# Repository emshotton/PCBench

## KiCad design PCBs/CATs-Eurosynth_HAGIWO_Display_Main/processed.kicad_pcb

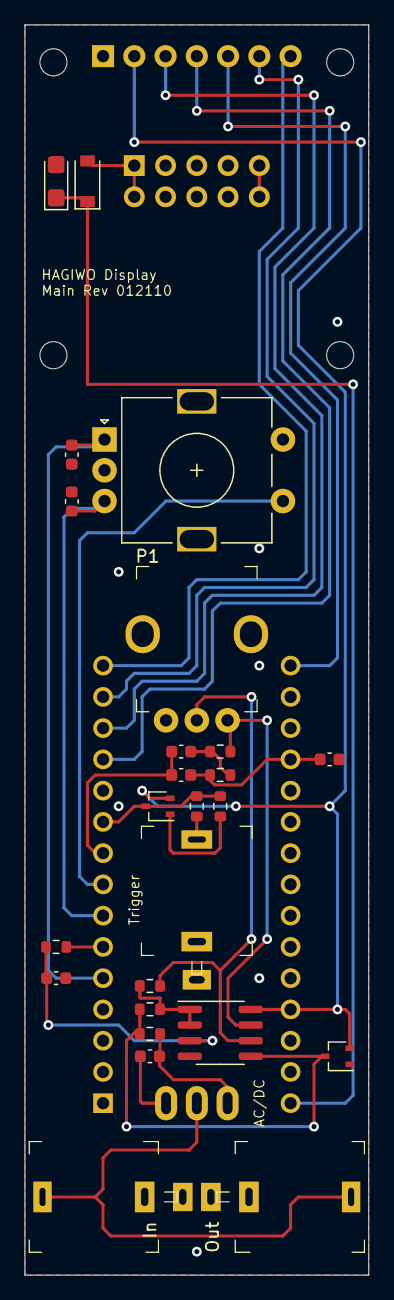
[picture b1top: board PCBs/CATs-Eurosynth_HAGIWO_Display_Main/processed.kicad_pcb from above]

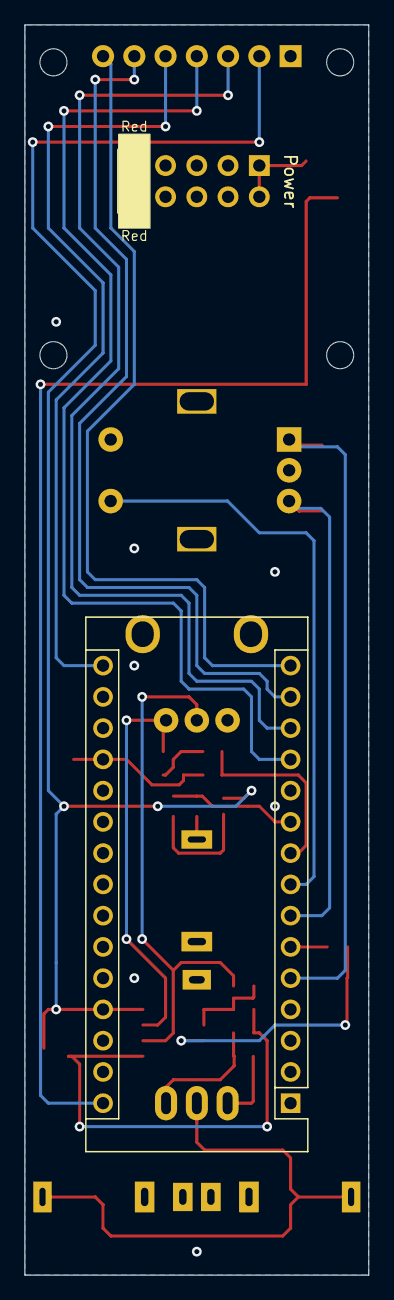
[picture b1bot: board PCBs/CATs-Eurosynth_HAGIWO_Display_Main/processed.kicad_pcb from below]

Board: 2 copper layers, 27.9 x 101.6 mm, 33 parts (2 on the bottom side), 26 nets.

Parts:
A1: Arduino_Nano_v3.x; Arduino_Nano
C1: 10µF/16V; CP_EIA-3216-18_Kemet-A
C2: 1µF; C_0603_1608Metric
C3: 4.7µF; C_0603_1608Metric
C4, C5: 22n; C_0603_1608Metric
C6: 470p; C_0603_1608Metric
C7, C8: 10n; C_0603_1608Metric
D1: B5817W; D_SOD-123
D2, D3: BAV99W; SOT-323_SC-70
DISP1: MSP096x
H1, H2, H3, H4: MountingHole; MountingHole_2.2mm_M2
J1: Power; Power_2x5_Vertical
J2: Trigger; Jack_3.5mm_QingPu_WQP-PJ301M-12
J3: In; Jack_3.5mm_QingPu_WQP-PJ301M-12
J4: Out; Jack_3.5mm_QingPu_WQP-PJ301M-12
P1: B100k; Potentiometer_AlpsAlpine_RK09K1130
R1, R5: 47k; R_0603_1608Metric
R2, R7, R8: 1k; R_0603_1608Metric
R3: 100k; R_0603_1608Metric
R4, R6: 10k; R_0603_1608Metric
SW1: AC/DC; SMTS-102-2xxx
SW2: Encoder; RotaryEncoder_Alps_EC11E-Switch_Vertical_H20mm
U1: MCP6002-xSN; SOIC-8_3.9x4.9mm_P1.27mm

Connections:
+5V: A1.27, D2.2, D3.2, DISP1.VCC, U1.8
+12V: A1.30, C1.1, D1.1
+12VA: D1.2, J1.+12V
CS: A1.15, DISP1.CS
DC: A1.14, DISP1.DC
DI: A1.12, DISP1.DI
DO: A1.13, DISP1.DO
ENC_A: A1.5, C7.1, SW2.A
ENC_B: A1.7, C8.1, SW2.B
ENC_SW: A1.8, SW2.S1
Fast_PWM: A1.6, R1.2
GND: A1.4, A1.29, C1.2, C2.2, C6.2, C7.2, C8.2, D2.1, D3.1, DISP1.GND, J1.GND, J2.S, J2.TN, J3.S, J3.TN, J4.S, R3.1, SW2.C, SW2.S2, U1.4
In: A1.19, C5.1, C6.1, R8.1
LPF_Enable: A1.9, C4.2, C5.2
unnamed: C2.1, R1.1, U1.3
unnamed: C3.1, R5.2, SW1.1
unnamed: C3.2, SW1.3
unnamed: C4.1, R7.1, R8.2
unnamed: D3.3, R4.2, R5.1, U1.5
unnamed: J2.T, R2.2
unnamed: J3.T, J4.T, SW1.2
unnamed: P1.CW, R7.2, U1.7
unnamed: P1.W, R6.2, U1.6
Offset: R4.1, R6.1, U1.1, U1.2
RST: A1.16, DISP1.RESET
TriggerIn: A1.10, D2.3, R2.1, R3.2

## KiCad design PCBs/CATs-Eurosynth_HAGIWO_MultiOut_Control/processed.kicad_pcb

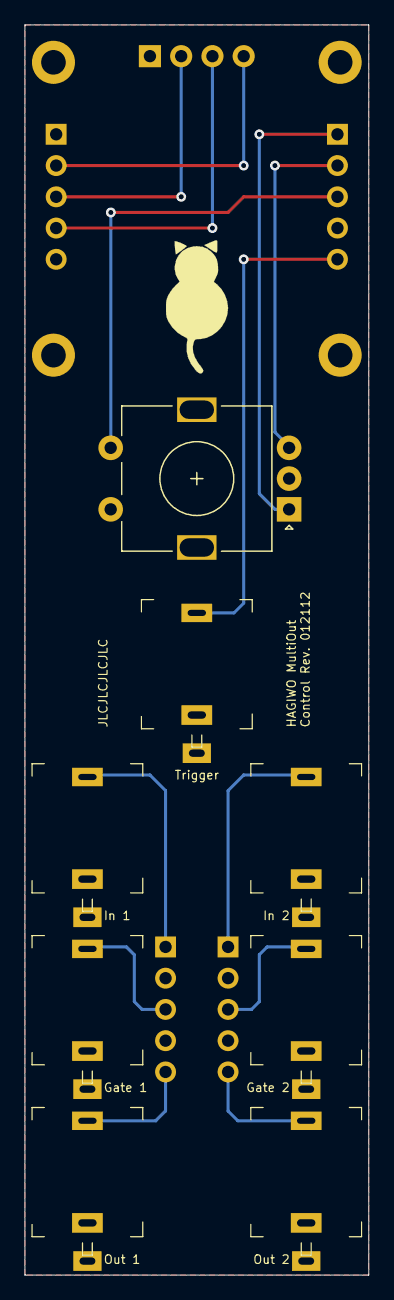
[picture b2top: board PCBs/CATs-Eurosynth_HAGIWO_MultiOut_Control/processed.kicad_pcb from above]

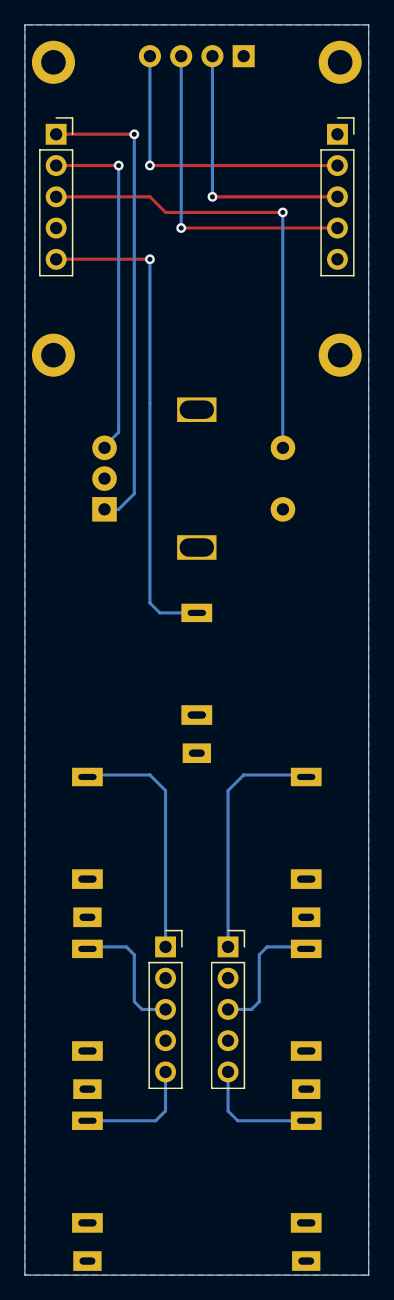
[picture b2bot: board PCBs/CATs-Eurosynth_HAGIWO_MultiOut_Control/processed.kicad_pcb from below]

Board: 2 copper layers, 27.9 x 101.6 mm, 13 parts (4 on the bottom side), 14 nets.

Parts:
D1: SSD1306_4Pin; 0.96inch_OLED_MC096GX
J1: Trigger; Jack_3.5mm_QingPu_WQP-PJ301M-12
J2: In 1; Jack_3.5mm_QingPu_WQP-PJ301M-12
J3: Gate 1; Jack_3.5mm_QingPu_WQP-PJ301M-12
J4: Out 1; Jack_3.5mm_QingPu_WQP-PJ301M-12
J5: In 2; Jack_3.5mm_QingPu_WQP-PJ301M-12
J6: Gate 2; Jack_3.5mm_QingPu_WQP-PJ301M-12
J7: Out 2; Jack_3.5mm_QingPu_WQP-PJ301M-12
J8: EncTrig; PinSocket_1x05_P2.54mm_Vertical
J9: Ch. 1; PinSocket_1x05_P2.54mm_Vertical
J10: Ch. 2; PinSocket_1x05_P2.54mm_Vertical
J11: I2C; PinSocket_1x05_P2.54mm_Vertical
SW1: Enc; RotaryEncoder_Alps_EC11E-Switch_Vertical_H20mm

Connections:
+3V3: D1.VCC, J11.3
Enc_A: J8.1, SW1.A
Enc_B: J8.2, SW1.B
Enc_SW: J8.3, SW1.S1
GND: D1.GND, J1.S, J1.TN, J2.S, J2.TN, J3.S, J4.S, J5.S, J5.TN, J6.S, J7.S, J8.4, J9.2, J9.4, J10.2, J10.4, J11.1, J11.5, SW1.C, SW1.S2
Gate1: J3.T, J9.3
Gate2: J6.T, J10.3
In1: J2.T, J9.1
In2: J5.T, J10.1
Out1: J4.T, J9.5
Out2: J7.T, J10.5
SCL: D1.SCL, J11.4
SDA: D1.SDA, J11.2
Trigger: J1.T, J8.5

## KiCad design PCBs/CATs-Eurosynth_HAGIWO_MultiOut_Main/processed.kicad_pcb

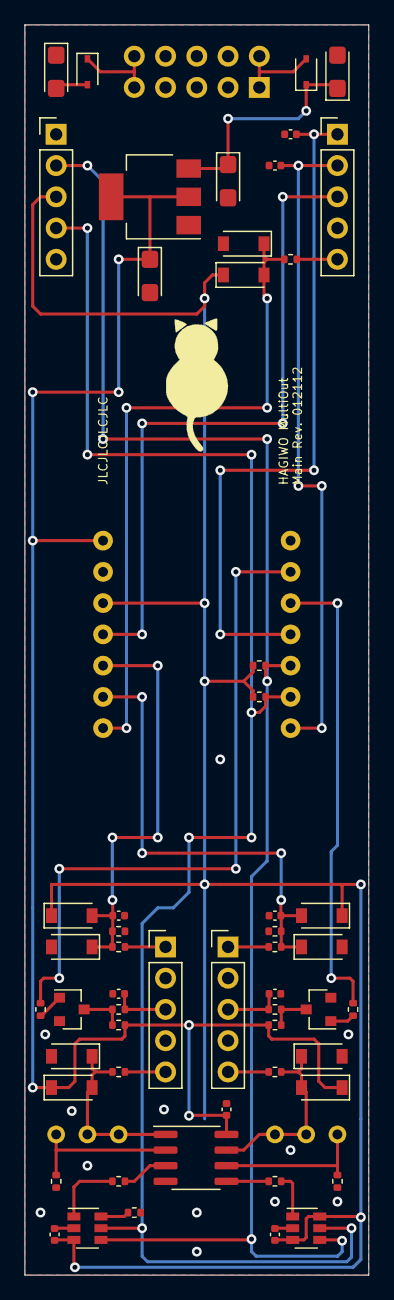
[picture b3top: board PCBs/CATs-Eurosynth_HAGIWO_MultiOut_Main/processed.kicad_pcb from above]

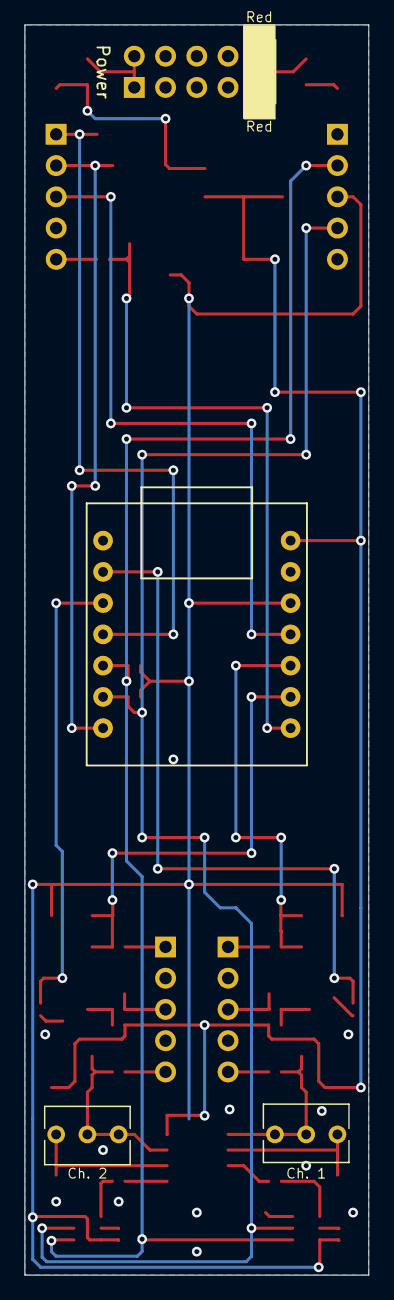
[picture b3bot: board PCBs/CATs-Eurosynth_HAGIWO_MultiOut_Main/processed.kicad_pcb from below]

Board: 2 copper layers, 27.9 x 101.6 mm, 59 parts (4 on the bottom side), 37 nets.

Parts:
C1, C2, C3, C4: 10µ; CP_EIA-3216-18_Kemet-A
C5, C6, C7, C8: 10n; C_0402_1005Metric
C9, C10: 1µ; C_0402_1005Metric
C11, C12, C13: 100n; C_0402_1005Metric
D1, D2: 1N5819WS; D_SOD-323
D4, D5, D6, D7, D8, D9, D10, D11, D12, D13: BAT43W; D_SOD-123
J1: Power; Power_2x5_Vertical
J9: EncTrig; PinHeader_1x05_P2.54mm_Vertical
J10: Ch. 1; PinHeader_1x05_P2.54mm_Vertical
J11: I2C; PinHeader_1x05_P2.54mm_Vertical
J12: Ch. 2; PinHeader_1x05_P2.54mm_Vertical
Q1, Q2: MMBT3904; SOT-23
R1, R2: 3k3; R_0402_1005Metric
R3, R16, R20: 10k; R_0402_1005Metric
R4, R17: 6k8; R_0402_1005Metric
R5, R6: 220k; R_0402_1005Metric
R7, R8: 330k; R_0402_1005Metric
R9: 33k; R_0402_1005Metric
R10, R11: 1k; R_0402_1005Metric
R12, R13, R14, R15: 330R; R_0402_1005Metric
R18, R19: 470R; R_0402_1005Metric
RV1, RV2: 5k; Potentiometer_Bourns_3266Y_Vertical
U1: AMS1117-5.0; SOT-223-3_TabPin2
U2: SeeeduinoXIAOPin; Seeeduino XIAO Pin
U3, U5: MCP4725xxx-xCH; SOT-23-6
U4: MCP6002-xSN; SOIC-8_3.9x4.9mm_P1.27mm

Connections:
+3V3: C11.1, C12.1, D4.1, D6.1, D8.1, J11.3, R1.1, R2.1, U2.12, U3.3, U5.3, U5.6
+5V: C4.1, C13.1, D10.1, D12.1, R12.1, R13.1, U1.2, U2.14, U4.8
+12V: C1.1, C3.1, D1.1, U1.3
-12V: C2.2, D2.2
A7: D8.2, D9.1, R9.1, U2.8
A8: C6.1, D6.2, D7.1, R6.1, R8.2, U2.9
A9: C5.1, D4.2, D5.1, R5.1, R7.2, U2.10
D1: R10.2, U2.2
D2: R11.2, U2.3
D3: C7.1, J9.1, U2.4
D6: C8.1, J9.2, U2.7
D10: J9.3, U2.11
GND: C1.2, C2.1, C3.2, C4.2, C5.2, C6.2, C7.2, C8.2, C9.2, C10.2, C11.2, C12.2, C13.2, D5.2, D7.2, D9.2, D11.2, D13.2, J1.GND, J9.4, J10.2, J10.4, J11.1, J11.5, J12.2, J12.4, Q1.2, Q2.2, R4.1, R7.1, R8.1, R17.1, R20.1, U1.1, U2.13, U3.2, U4.4, U5.2
Gate1: C9.1, J10.3, R14.1
Gate2: C10.1, J12.3, R15.1
In1: J10.1, R5.2
In2: J12.1, R6.2
unnamed: D1.2, J1.+12V
unnamed: D2.1, J1.-12V
unnamed: D10.2, D11.1, R18.2, RV1.1, RV1.2, U4.1
unnamed: D12.2, D13.1, R19.2, RV2.1, RV2.2, U4.7
unnamed: Q1.1, R10.1
unnamed: Q1.3, R12.2, R14.2
unnamed: Q2.1, R11.1
unnamed: Q2.3, R13.2, R15.2
unnamed: R3.1, U4.3
unnamed: R3.2, U3.1
unnamed: R4.2, RV1.3, U4.2
unnamed: R16.1, U4.5
unnamed: R16.2, U5.1
unnamed: R17.2, RV2.3, U4.6
unnamed: R20.2, U3.6
Out1: J10.5, R18.1
Out2: J12.5, R19.1
SCL: J11.4, R2.2, U2.6, U3.5, U5.5
SDA: J11.2, R1.2, U2.5, U3.4, U5.4
Trigger: J9.5, R9.2

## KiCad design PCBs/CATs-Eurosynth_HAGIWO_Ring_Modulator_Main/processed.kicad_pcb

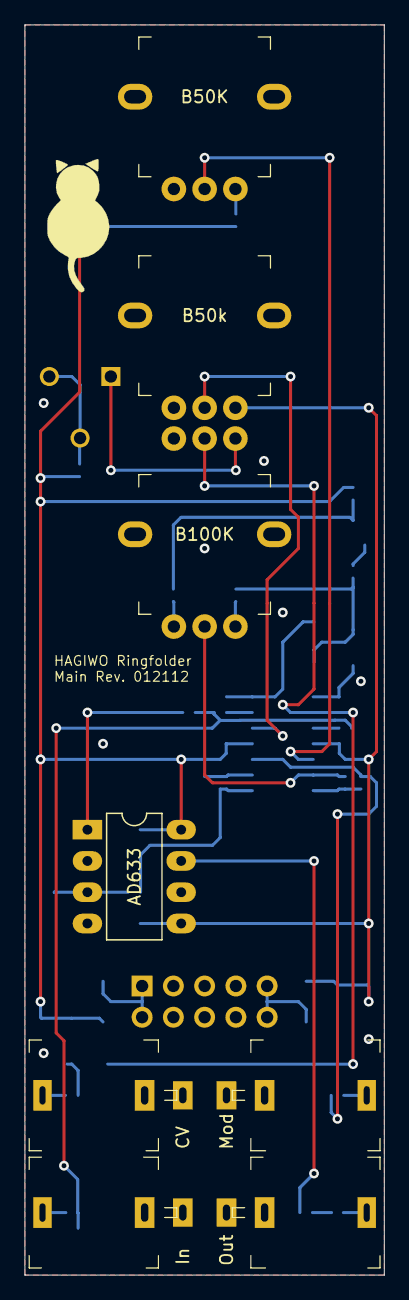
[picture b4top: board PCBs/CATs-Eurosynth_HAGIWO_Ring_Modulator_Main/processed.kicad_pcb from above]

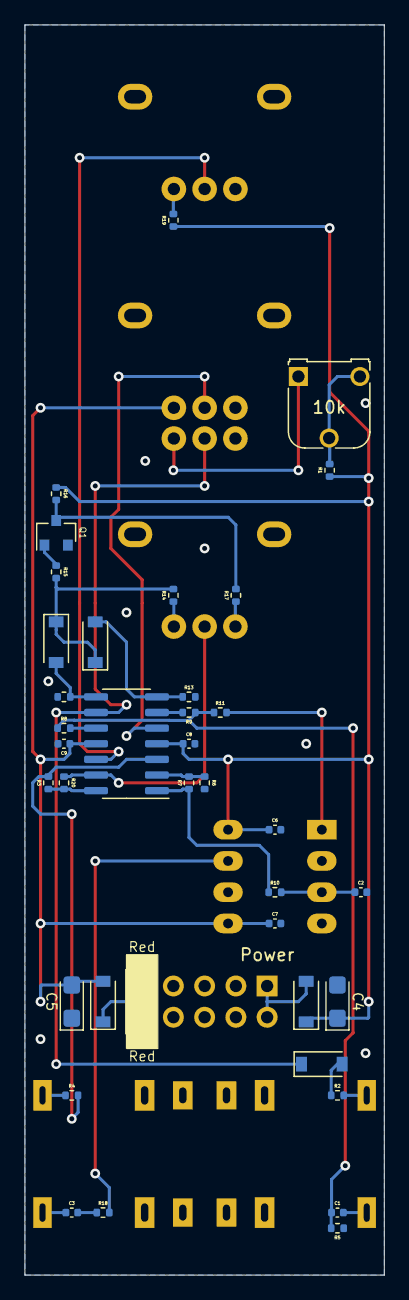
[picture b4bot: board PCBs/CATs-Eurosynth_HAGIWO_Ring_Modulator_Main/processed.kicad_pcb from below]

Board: 2 copper layers, 29.2 x 101.6 mm, 46 parts (38 on the bottom side), 35 nets.

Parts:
C1, C3: 1µ; C_0402_1005Metric
C2: 3n3; C_0402_1005Metric
C4, C5: 10µ/25V; CP_EIA-3216-18_Kemet-A
C6, C7, C8, C9: 100n; C_0402_1005Metric
D1, D2, D3: 1N4148; D_SOD-123
D4, D5: 1N5817; D_SOD-123
J1: CV; Jack_3.5mm_QingPu_WQP-PJ301M-12
J2: In; Jack_3.5mm_QingPu_WQP-PJ301M-12
J3: Mod; Jack_3.5mm_QingPu_WQP-PJ301M-12
J4: Out; Jack_3.5mm_QingPu_WQP-PJ301M-12
J5: Power; Power_2x5_Vertical
P1: B50k; Potentiometer_AlpsAlpine_RK09L1240
P2: B100K; Potentiometer_AlpsAlpine_RK09L1140
P3: B50K; Potentiometer_AlpsAlpine_RK09L1140
Q1: MMBT3904; SOT-23
R1, R2, R7, R10, R15: 10k; R_0402_1005Metric
R3, R4, R6, R8, R9, R11: 33k; R_0402_1005Metric
R5, R12, R13, R16, R20: 100k; R_0402_1005Metric
R14, R17, R19: 47k; R_0402_1005Metric
R18: 4k7; R_0402_1005Metric
T1: 10k; Potentiometer_Runtron_RM-065_Vertical
U1: AD633; DIP-8_W7.62mm_LongPads
U2: TL074; SOIC-14_3.9x8.7mm_P1.27mm

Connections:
+12V: C4.1, C6.2, C8.2, D4.1, R1.2, R16.2, R19.2, U1.8, U2.4
-12V: C5.2, C7.1, C9.1, D5.2, P1.CW1, U1.5, U2.11
Fold_In: R3.2, R20.1, U2.14
GND: C2.1, C4.2, C5.1, C6.1, C7.2, C8.1, C9.2, J1.S, J1.TN, J2.S, J2.TN, J3.S, J3.TN, J4.S, J5.GND, P1.CCW1, P1.CCW2, P3.CCW, Q1.2, R5.1, R6.1, R12.1, R13.1, U1.2, U1.4, U1.6
unnamed: C1.1, R5.2, R8.2, R9.2, R11.2
unnamed: C1.2, J2.T
unnamed: C2.2, R10.1, U1.3
unnamed: C3.1, J4.T
unnamed: C3.2, R18.1
unnamed: D1.1, P1.W2, U2.9
unnamed: D1.2, R2.1
unnamed: D2.1, D3.1, R14.2, R15.2
unnamed: D2.2, R12.2, U2.8
unnamed: D3.2, R13.2, U2.7
unnamed: D4.2, J5.+12V
unnamed: D5.1, J5.-12V
unnamed: J1.T, R2.2
unnamed: J3.T, R4.2
unnamed: P1.CW2, T1.1
unnamed: P1.W1, U2.5
unnamed: P2.CCW, R17.1
unnamed: P2.CW, R14.1
unnamed: P2.W, R20.2, U2.13
unnamed: P3.CW, R19.1
unnamed: P3.W, U2.12
unnamed: Q1.1, R15.1
unnamed: Q1.3, R16.1, R17.2
unnamed: R1.1, T1.2, T1.3
unnamed: R3.1, R4.1, U2.3
unnamed: R6.2, R7.2, U2.2
unnamed: R8.1, U2.10
unnamed: R9.1, U2.6
unnamed: R7.1, R10.2, U2.1
unnamed: R11.1, U1.1
unnamed: R18.2, U1.7

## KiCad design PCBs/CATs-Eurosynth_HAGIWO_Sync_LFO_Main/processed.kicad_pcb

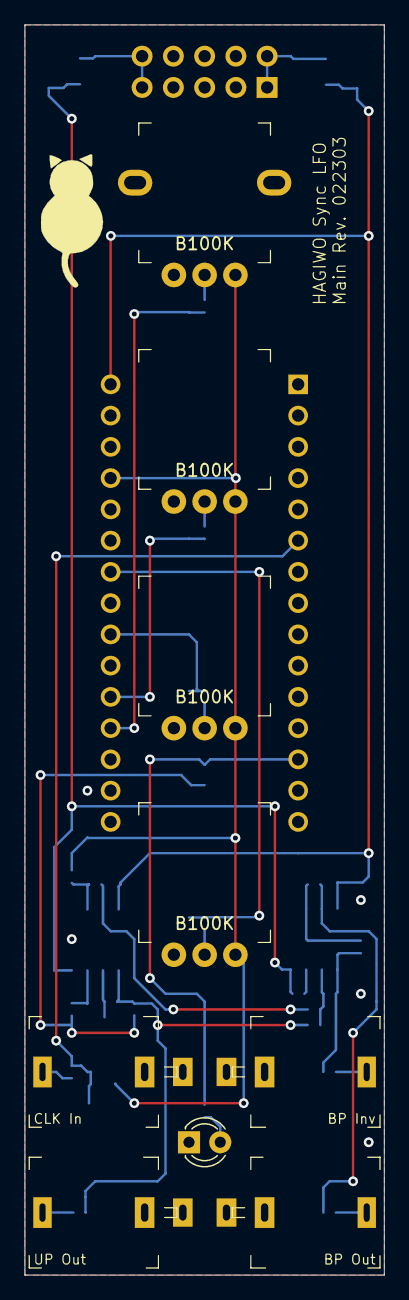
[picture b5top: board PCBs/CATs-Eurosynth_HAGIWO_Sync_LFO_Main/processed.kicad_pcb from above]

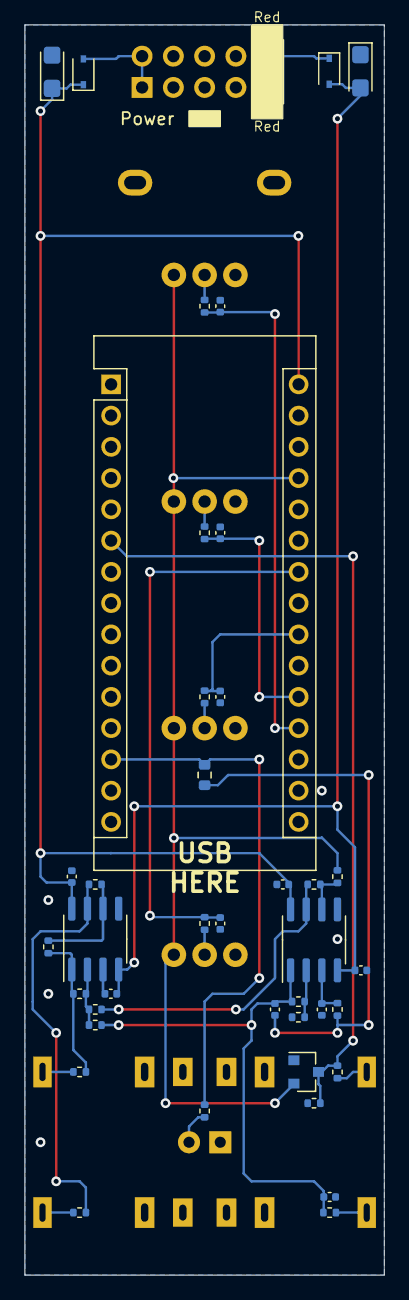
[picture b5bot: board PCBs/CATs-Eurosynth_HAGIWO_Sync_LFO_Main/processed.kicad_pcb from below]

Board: 2 copper layers, 29.2 x 101.6 mm, 50 parts (41 on the bottom side), 31 nets.

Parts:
A1: Arduino_Nano_v3.x; Arduino_Nano
C1, C2, C3, C4: 220p; C_0402_1005Metric
C5: 6.8n; C_0402_1005Metric
C6: 10n; C_0402_1005Metric
C7, C9, C10, C12, C13: 100n; C_0402_1005Metric
C8, C11: 10u; CP_EIA-3216-18_Kemet-A
D1: BAV99,215; SOT-23
D2: LED; LED_D3.0mm
D3, D4: 1N5819; D_SOD-323
J1: UP Out; Jack_3.5mm_QingPu_WQP-PJ301M-12
J2: CLK In; Jack_3.5mm_QingPu_WQP-PJ301M-12
J3: BP Inv; Jack_3.5mm_QingPu_WQP-PJ301M-12
J4: BP Out; Jack_3.5mm_QingPu_WQP-PJ301M-12
J5: Power; Power_2x5_Vertical
P1, P3, P4: B100K; Potentiometer_AlpsAlpine_RK09L1140_wo_Fix
P2: B100K; Potentiometer_AlpsAlpine_RK09L1140
R1, R2, R3, R4: 470R; R_0402_1005Metric
R5: 13k; R_0603_1608Metric
R6: 27k; R_0402_1005Metric
R7, R10, R16, R21: 1k; R_0402_1005Metric
R8: 300R; R_0402_1005Metric
R9, R11, R13, R14, R15, R17, R18, R19, R20: 10k; R_0402_1005Metric
R12: 100k; R_0402_1005Metric
U1, U2: TL072; SOIC-8_3.9x4.9mm_P1.27mm

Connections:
+5V: A1.27, D1.2, P1.CW, P2.CW, P3.CW, P4.CW, R18.2
+12V: A1.30, C8.1, C9.2, C10.2, D3.1, U1.8, U2.8
-5VA: R15.2, R17.1, U1.7
-12V: C11.2, C12.1, C13.1, D4.2, U1.4, U2.4
A0: A1.19, C2.1, R2.1
A1: A1.20, C3.1, R3.1
A3: A1.22, C1.1, R1.1
A5: A1.24, C4.1, R4.1
D3: A1.6, D1.3, R10.1, R12.2
D10: A1.13, R5.2, R8.2
GND: A1.4, A1.29, C1.2, C2.2, C3.2, C4.2, C6.1, C7.1, C8.2, C9.1, C10.1, C11.1, C12.2, C13.2, D1.1, D2.1, J1.S, J2.S, J2.TN, J3.S, J4.S, J5.GND, P1.CCW, P2.CCW, P3.CCW, P4.CCW, R11.1, R12.1, U1.5, U2.3, U2.5
unnamed: C5.2, R5.1, R6.2
unnamed: C6.2, R6.1, U1.3
unnamed: D2.2, R8.1
unnamed: D3.2, J5.+12V
unnamed: D4.1, J5.-12V
unnamed: J1.T, R7.1
unnamed: J2.T, R10.2
unnamed: J3.T, R16.1
unnamed: J4.T, R21.1
unnamed: P1.W, R1.2
unnamed: P2.W, R2.2
unnamed: P3.W, R3.2
unnamed: P4.W, R4.2
unnamed: R9.2, R11.2, U1.2
unnamed: R13.1, R14.2, R15.1, U2.2
unnamed: R14.1, R16.2, R20.2, U2.1
unnamed: R17.2, R18.1, U1.6
unnamed: R19.1, R21.2, U2.7
unnamed: R19.2, R20.1, U2.6
Out: C5.1, C7.2, R7.2, R9.1, R13.2, U1.1

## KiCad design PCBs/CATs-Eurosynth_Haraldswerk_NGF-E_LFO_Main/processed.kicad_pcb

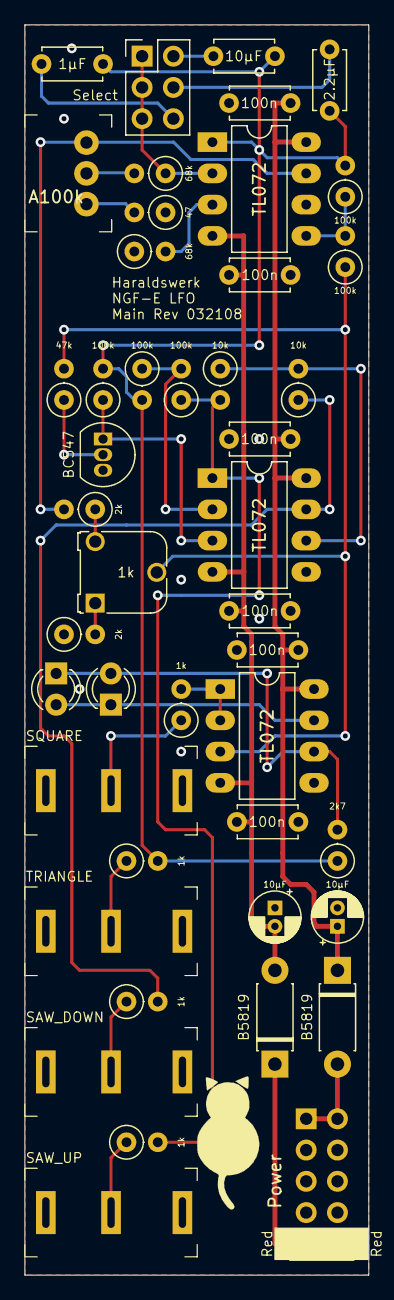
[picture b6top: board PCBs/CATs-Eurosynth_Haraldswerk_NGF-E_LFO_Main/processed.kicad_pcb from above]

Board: 2 copper layers, 27.9 x 101.6 mm, 45 parts (0 on the bottom side), 29 nets.

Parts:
C1: 1µF; C_Disc_D4.7mm_W2.5mm_P5.00mm
C2, C3: 10µF; CP_Radial_D4.0mm_P1.50mm
C4, C5, C6, C7, C8, C9: 100n; C_Disc_D4.7mm_W2.5mm_P5.00mm
C10: 10µF; C_Disc_D4.7mm_W2.5mm_P5.00mm
C11: 2.2µF; C_Disc_D4.7mm_W2.5mm_P5.00mm
D1, D2: LED; LED_D3.0mm
D3, D4: B5819; D_DO-41_SOD81_P7.62mm_Horizontal
J1: SAW_UP; Jack_3.5mm_QingPu_WQP-PJ323M
J2: SAW_DOWN; Jack_3.5mm_QingPu_WQP-PJ323M
J3: TRIANGLE; Jack_3.5mm_QingPu_WQP-PJ323M
J4: SQUARE; Jack_3.5mm_QingPu_WQP-PJ323M
J5: Power; Power_2x5_Vertical
J6: Select; PinHeader_2x03_P2.54mm_Vertical
Q1: BC547; TO-92_Inline
R1: 47; R_Axial_DIN0207_L6.3mm_D2.5mm_P2.54mm_Vertical
R2, R3: 68k; R_Axial_DIN0207_L6.3mm_D2.5mm_P2.54mm_Vertical
R4, R5, R9, R10, R11: 100k; R_Axial_DIN0207_L6.3mm_D2.5mm_P2.54mm_Vertical
R6, R7: 2k; R_Axial_DIN0207_L6.3mm_D2.5mm_P2.54mm_Vertical
R8: 47k; R_Axial_DIN0207_L6.3mm_D2.5mm_P2.54mm_Vertical
R12, R15, R16, R17: 1k; R_Axial_DIN0207_L6.3mm_D2.5mm_P2.54mm_Vertical
R13, R14: 10k; R_Axial_DIN0207_L6.3mm_D2.5mm_P2.54mm_Vertical
R18: 2k7; R_Axial_DIN0207_L6.3mm_D2.5mm_P2.54mm_Vertical
RV1: A100k; Potentiometer_AlpsAlpine_RK0971110
T1: 1k; Potentiometer_Runtron_RM-065_Vertical
U1, U2, U3: TL072; DIP-8_W7.62mm_LongPads

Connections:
+12V: C2.1, C4.1, C6.1, C8.1, D3.1, U1.8, U2.8, U3.8
+12VA: D3.2, J5.+12V
-12V: C3.2, C5.2, C7.2, C9.2, D4.2, U1.4, U2.4, U3.4
-12VA: D4.1, J5.-12V
GND: C2.2, C3.1, C4.2, C5.1, C6.2, C7.1, C8.2, C9.1, J1.S, J2.S, J3.S, J4.S, J5.GND, Q1.3, R1.1, R3.1, R7.1, U1.6, U2.5, U3.5
unnamed: C1.2, J6.6
unnamed: C10.2, J6.2
unnamed: C11.2, J6.4
unnamed: D1.1, D2.2, U3.7
unnamed: D1.2, D2.1, R18.2, U3.6
unnamed: J1.T, R12.1
unnamed: J2.T, R15.1
unnamed: J3.T, R16.1
unnamed: J4.T, R17.1
unnamed: J6.1, J6.3, J6.5, R2.1, U1.2
unnamed: Q1.1, R10.1, U2.3
unnamed: Q1.2, R8.1
unnamed: R3.2, U1.3
unnamed: R4.1, R5.2, U1.5
unnamed: R6.1, T1.3
unnamed: R6.2, U1.7
unnamed: R7.2, T1.1
unnamed: R11.1, R12.2, R13.2, U2.1
unnamed: R9.1, R11.2, U2.2
unnamed: R13.1, R14.2, U2.6
unnamed: R14.1, R15.2, U2.7
unnamed: R17.2, U3.1, U3.2
SQR: R5.1, R8.2, T1.2, U3.3
TRI: C1.1, C10.1, C11.1, R4.2, R9.2, R10.2, R16.2, R18.1, U1.1

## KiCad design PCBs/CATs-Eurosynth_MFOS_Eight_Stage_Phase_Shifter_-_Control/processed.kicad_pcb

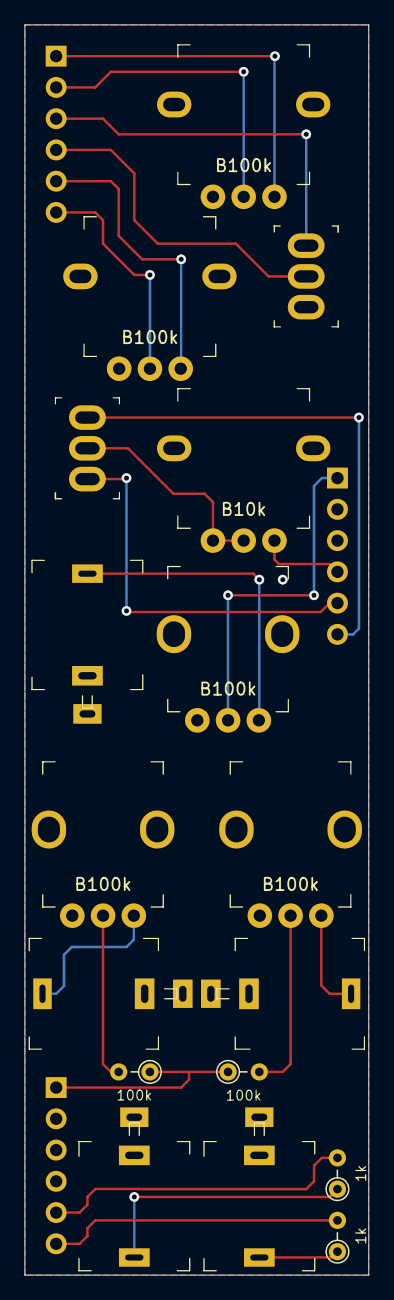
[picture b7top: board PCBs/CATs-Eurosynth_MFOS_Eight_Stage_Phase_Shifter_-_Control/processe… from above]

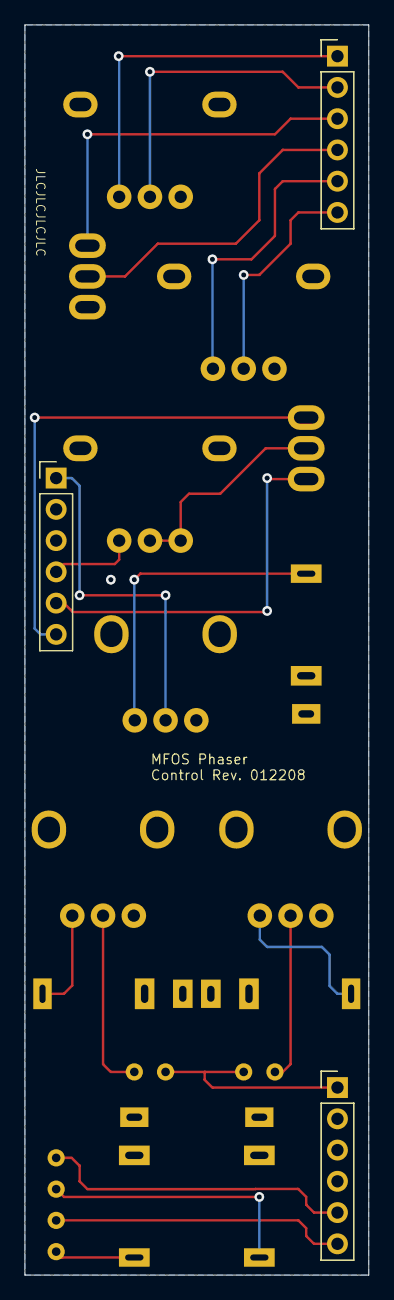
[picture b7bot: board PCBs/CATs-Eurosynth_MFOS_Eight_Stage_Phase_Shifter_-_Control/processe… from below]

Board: 2 copper layers, 27.9 x 101.6 mm, 20 parts (3 on the bottom side), 22 nets.

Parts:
J1: LFO; PinHeader_1x06_P2.54mm_Vertical
J2: CV_OUT; PinHeader_1x06_P2.54mm_Vertical
J3: In; PinHeader_1x06_P2.54mm_Vertical
J4: CV1; Jack_3.5mm_QingPu_WQP-PJ301M-12
J5: CV2; Jack_3.5mm_QingPu_WQP-PJ301M-12
J6: In; Jack_3.5mm_QingPu_WQP-PJ301M-12
J7: Out1; Jack_3.5mm_QingPu_WQP-PJ301M-12
J8: Out2; Jack_3.5mm_QingPu_WQP-PJ301M-12
P1, P2, P3: B100k; Potentiometer_AlpsAlpine_RK09K1130
P4, P6: B100k; Potentiometer_AlpsAlpine_RK09L1140
P5: B10k; Potentiometer_AlpsAlpine_RK09L1140
R1, R2: 1k; R_Axial_DIN0204_L3.6mm_D1.6mm_P2.54mm_Vertical
R3, R4: 100k; R_Axial_DIN0204_L3.6mm_D1.6mm_P2.54mm_Vertical
SW1: Stages; Switches_SMTS-10x
SW2: Mode; Switches_SMTS-10x

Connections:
CV: J2.1, R3.1, R4.1
Depth_CW: J1.5, P6.CW
Depth_W: J1.6, P6.W
FB: J3.4, P5.CW
GND: J2.2, J2.3, J2.4, J3.2, J3.3, J4.S, J4.TN, J5.S, J5.TN, J6.S, J6.TN, J7.S, J8.S, P1.CCW, P2.CCW, P3.CCW, P4.CCW, P6.CCW
In: J3.1, P3.W
Mode_In: J1.3, SW2.1
Mode_Out: J1.4, SW2.2
unnamed: J4.T, P1.CW
unnamed: J5.T, P2.CW
unnamed: J6.T, P3.CW
unnamed: J7.T, R1.1
unnamed: J8.T, R2.1
unnamed: P1.W, R3.2
unnamed: P2.W, R4.2
unnamed: P5.CCW, P5.W, SW1.2
OUT4: J3.5, SW1.1
OUT8: J3.6, SW1.3
Out1: J2.5, R1.2
Out2: J2.6, R2.2
Rate_CW: J1.1, P4.CW
Rate_W: J1.2, P4.W
